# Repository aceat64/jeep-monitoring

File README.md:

# Raspberry Pi Jeep Monitoring System

This system is designed for monitoring or interacting with various functions of my specific Jeep Wrangler, such as the dual battery system and the IHS (Internal High-Speed) CAN bus. All information is available via an API, for consumption by mobile devices or Android headunits on my Jeep's local wifi network.

## Features
- Voltage monitoring of two batteries, for dual battery systems.
- Current monitoring via a shunt resistor, tweaking the code may be required depending on your specific shunt resistor.
- Status of the battery isolator, a 12V digital input.
- Accelerometer, for determining vehicle tilt.
- GPS header, for external GPS module.
- CAN Bus transciever.

## Preview

### Top

### Bottom

## Bill Of Materials
See this [Google doc](https://docs.google.com/spreadsheets/d/1EL97Gz-JKfgCOYKvCzc1mUYXWVdC4jQAL_xUaZWqmfQ/edit?usp=sharing) for more info.

## License
Copyright Andrew LeCody 2017

All schematics, circuit board design files and documentation are released under the [Creative Commons Attribution-ShareAlike 4.0 International License](https://creativecommons.org/licenses/by-sa/4.0/).

All source code is releaed under the [GNU General Public License version 3](https://www.gnu.org/licenses/gpl-3.0-standalone.html).

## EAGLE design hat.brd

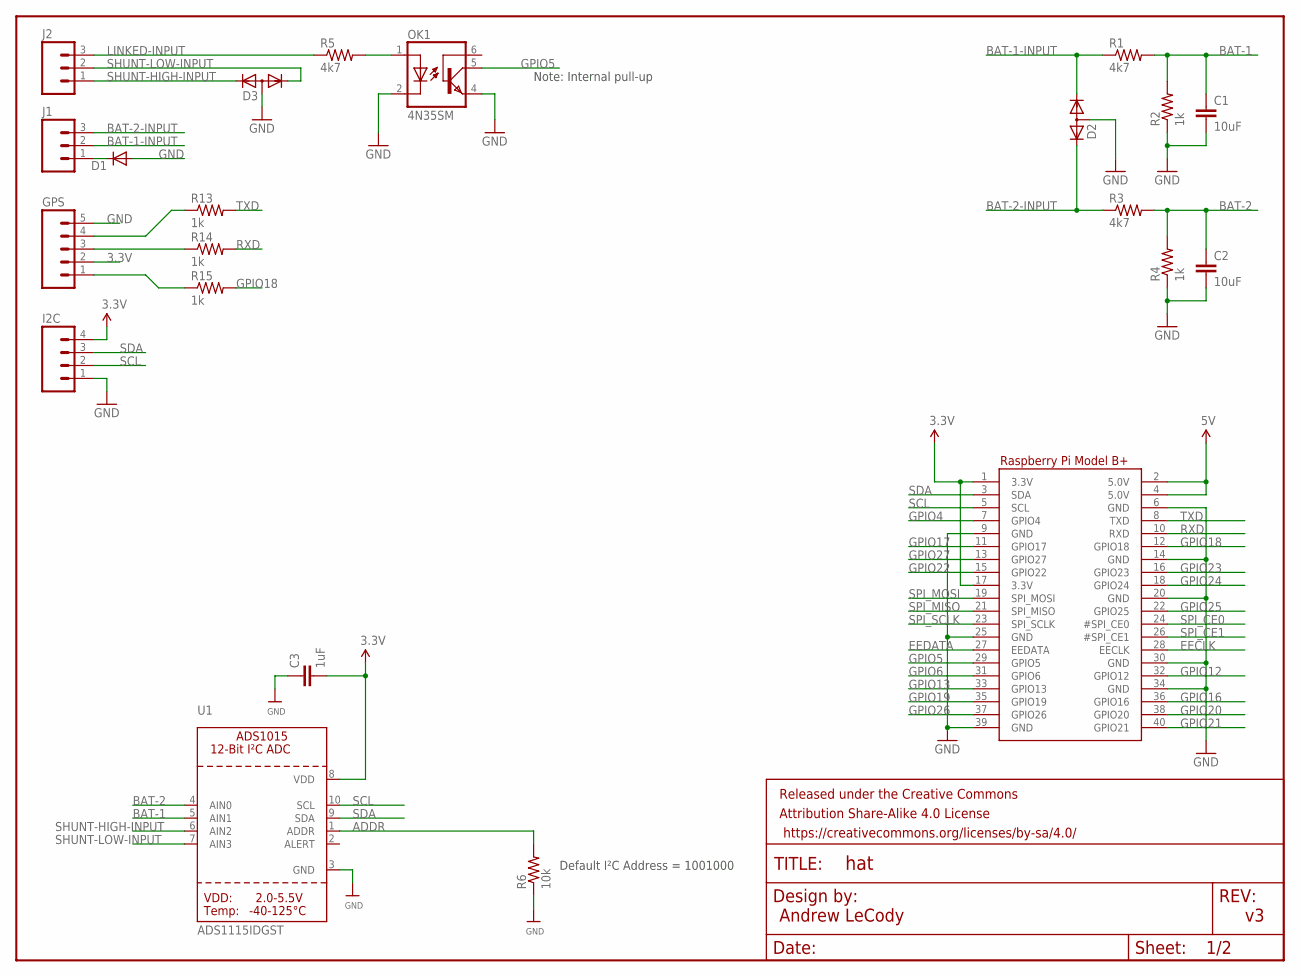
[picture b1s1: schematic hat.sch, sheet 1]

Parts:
C1, C2: 10uF; C0805
C3: 1uF; C0805
D1: DIODE-DO214AC; DO214AC
D2, D3: DIODE-2CA|ACSOT23; SOT23
FRAME1: FRAME-LETTERNO_PACKAGE; DUMMY
GPS: M05PTH; 1X05
I2C: M04PTH; 1X04
J1, J2: M03SCREW; SCREWTERMINAL-3.5MM-3
OK1: 4N35SM; DIL6-SMD
R1, R3, R5: 4k7; R0805
R2, R4, R13, R14, R15: 1k; R0805
R6: 10k; R0805
RPI1: RASPBERRYPI_BPLUS_HATNOSLOTS; PI_HAT_NOSLOTS
U1: ADS1115IDGST; MSOP10

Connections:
3.3V: C3.2, GPS.2, I2C.4, RPI1.1 (3.3V), RPI1.17 (3.3V), U1.8 (VDD); also elsewhere on the board
5V: RPI1.2 (5.0V), RPI1.4 (5.0V); also elsewhere on the board
ADDR: R6.2, U1.1 (ADDR)
BAT-1: C1.1, R1.2, R2.2, U1.5 (AIN1)
BAT-1-INPUT: D2.1 (K1), J1.2, R1.1
BAT-2: C2.1, R3.2, R4.2, U1.4 (AIN0)
BAT-2-INPUT: D2.2 (K2), J1.3, R3.1
EECLK: RPI1.28 (EECLK)
EEDATA: RPI1.27 (EEDATA)
GND: C1.2, C2.2, C3.1, D1.A, D2.3 (A), D3.3 (A), GPS.5, I2C.1, OK1.2 (C), OK1.4 (EMI), R2.1, R4.1, R6.1, RPI1.6 (GND), RPI1.9 (GND), RPI1.14 (GND), RPI1.20 (GND), RPI1.25 (GND), RPI1.30 (GND), RPI1.34 (GND), RPI1.39 (GND), U1.3 (GND); also elsewhere on the board
GPIO4: RPI1.7 (GPIO4)
GPIO5: OK1.5 (COL), RPI1.29 (GPIO5)
GPIO6: RPI1.31 (GPIO6)
GPIO12: RPI1.32 (GPIO12)
GPIO13: RPI1.33 (GPIO13)
GPIO16: RPI1.36 (GPIO16)
GPIO17: RPI1.11 (GPIO17)
GPIO18: R15.2, RPI1.12 (GPIO18)
GPIO19: RPI1.35 (GPIO19)
GPIO20: RPI1.38 (GPIO20)
GPIO21: RPI1.40 (GPIO21)
GPIO22: RPI1.15 (GPIO22)
GPIO23: RPI1.16 (GPIO23)
GPIO24: RPI1.18 (GPIO24)
GPIO25: RPI1.22 (GPIO25); also elsewhere on the board
GPIO26: RPI1.37 (GPIO26)
GPIO27: RPI1.13 (GPIO27)
LINKED-INPUT: J2.3, R5.1
unnamed: GPS.4, R13.1
unnamed: GPS.3, R14.1
unnamed: OK1.1 (A), R5.2
unnamed: GPS.1, R15.1
RXD: R14.2, RPI1.10 (RXD)
SCL: I2C.2, RPI1.5 (SCL), U1.10 (SCL)
SDA: I2C.3, RPI1.3 (SDA), U1.9 (SDA)
SHUNT-HIGH-INPUT: D3.2 (K2), J2.1, U1.6 (AIN2)
SHUNT-LOW-INPUT: D3.1 (K1), J2.2, U1.7 (AIN3)
SPI_CE0: RPI1.24 (#SPI_CE0); also elsewhere on the board
SPI_CE1: RPI1.26 (#SPI_CE1)
SPI_MISO: RPI1.21 (SPI_MISO); also elsewhere on the board
SPI_MOSI: RPI1.19 (SPI_MOSI); also elsewhere on the board
SPI_SCLK: RPI1.23 (SPI_SCLK); also elsewhere on the board
TXD: R13.2, RPI1.8 (TXD)
VEHICLE-GND: D1.C, J1.1

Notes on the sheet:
Andrew LeCody
Default I²C Address = 1001000
Note: Internal pull-up

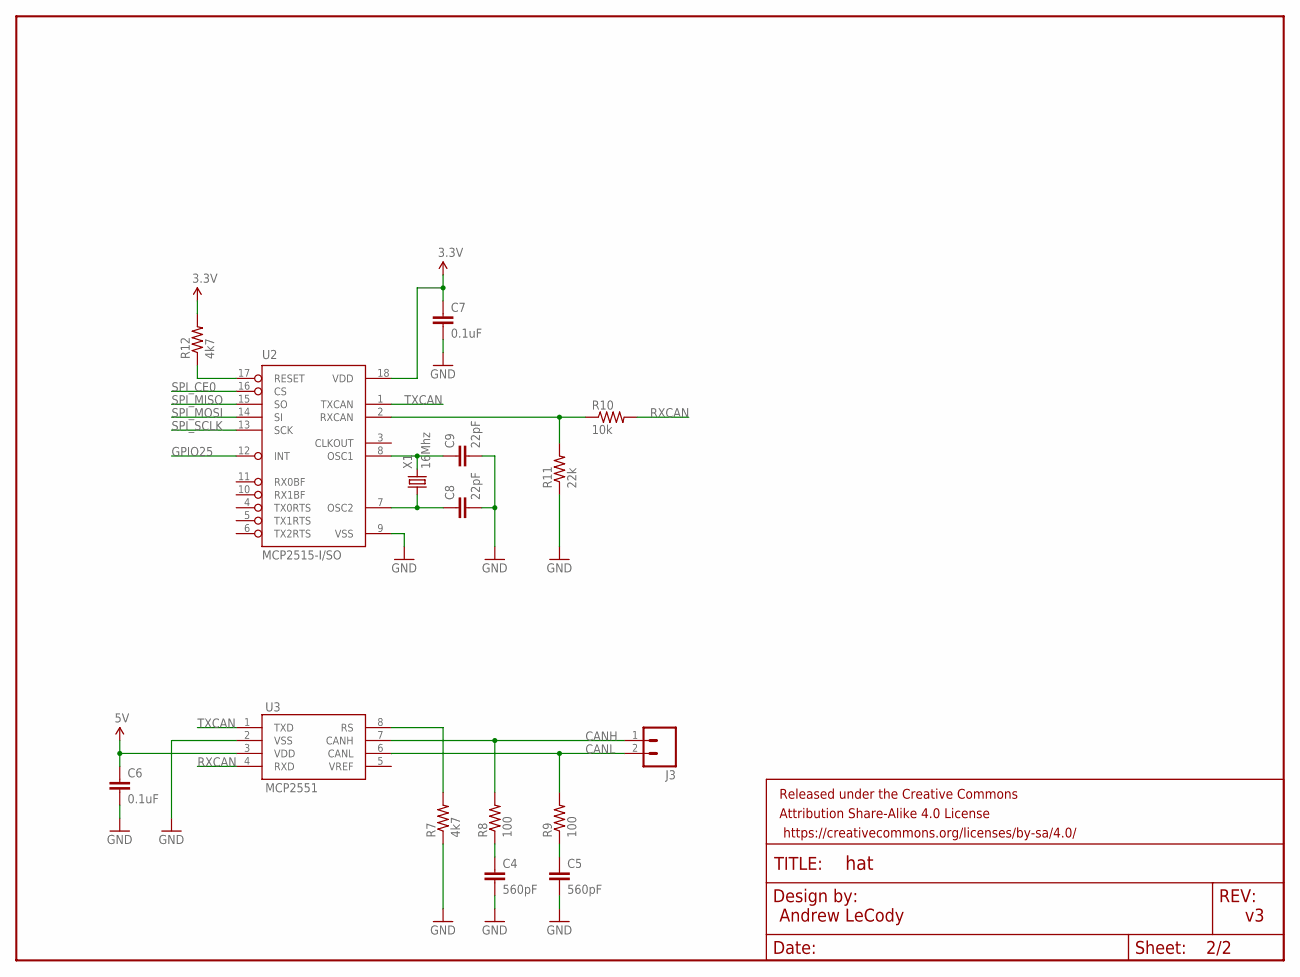
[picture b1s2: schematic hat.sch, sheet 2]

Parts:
C4, C5: 560pF; C0805
C6, C7: 0.1uF; C0805
C8, C9: 22pF; C0805
FRAME2: FRAME-LETTERNO_PACKAGE; DUMMY
J3: M023.5MM; SCREWTERMINAL-3.5MM-2
R7, R12: 4k7; R0805
R8, R9: 100; R0805
R10: 10k; R0805
R11: 22k; R0805
U2: MCP2515-I/SO; SO18L
U3: MCP2551; SO08
X1: 16Mhz; HC49-4-HSMX

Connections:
3.3V: C7.1, R12.2, U2.18 (VDD); also elsewhere on the board
5V: C6.1, U3.3 (VDD); also elsewhere on the board
CANH: J3.1, R8.2, U3.7 (CANH)
CANL: J3.2, R9.2, U3.6 (CANL)
GND: C4.2, C5.2, C6.2, C7.2, C8.2, C9.2, R7.1, R11.1, U2.9 (VSS), U3.2 (VSS); also elsewhere on the board
GPIO25: U2.12 (INT); also elsewhere on the board
unnamed: R10.1, R11.2, U2.2 (RXCAN)
unnamed: C4.1, R8.1
unnamed: C5.1, R9.1
unnamed: C9.1, U2.8 (OSC1), X1.2
unnamed: C8.1, U2.7 (OSC2), X1.1
RS: R7.2, U3.8 (RS)
RXCAN: R10.2, U3.4 (RXD)
SPI_CE0: U2.16 (CS); also elsewhere on the board
SPI_MISO: U2.15 (SO); also elsewhere on the board
SPI_MOSI: U2.14 (SI); also elsewhere on the board
SPI_SCLK: U2.13 (SCK); also elsewhere on the board
TXCAN: U2.1 (TXCAN), U3.1 (TXD)
U2_RST: R12.1, U2.17 (RESET)

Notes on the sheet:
Andrew LeCody

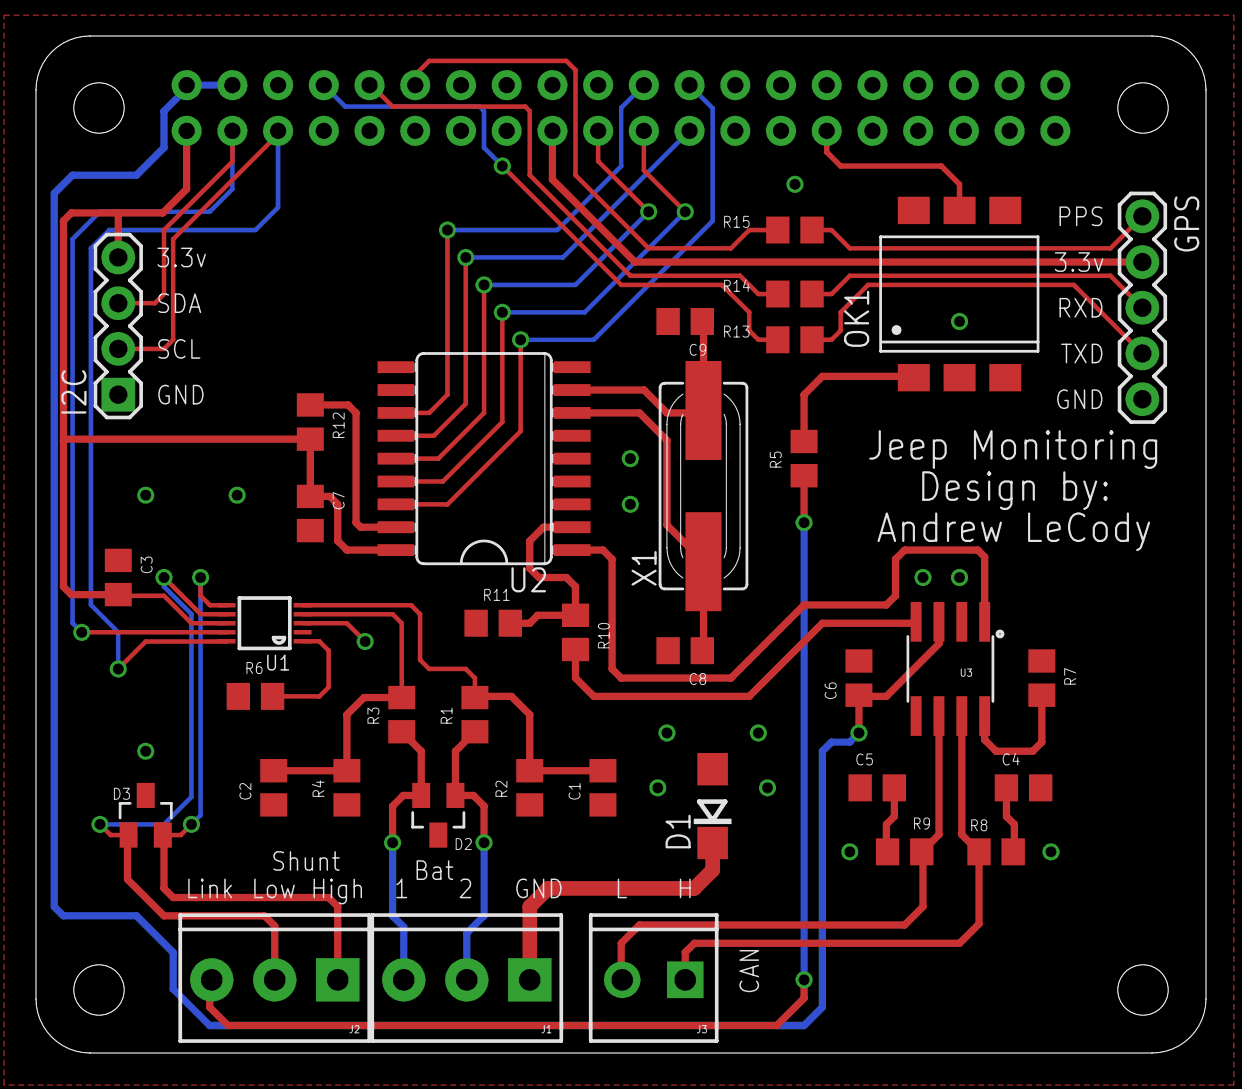
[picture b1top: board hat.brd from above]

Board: 2 copper layers, 65.0 x 56.5 mm, 40 parts (0 on the bottom side), 38 nets.

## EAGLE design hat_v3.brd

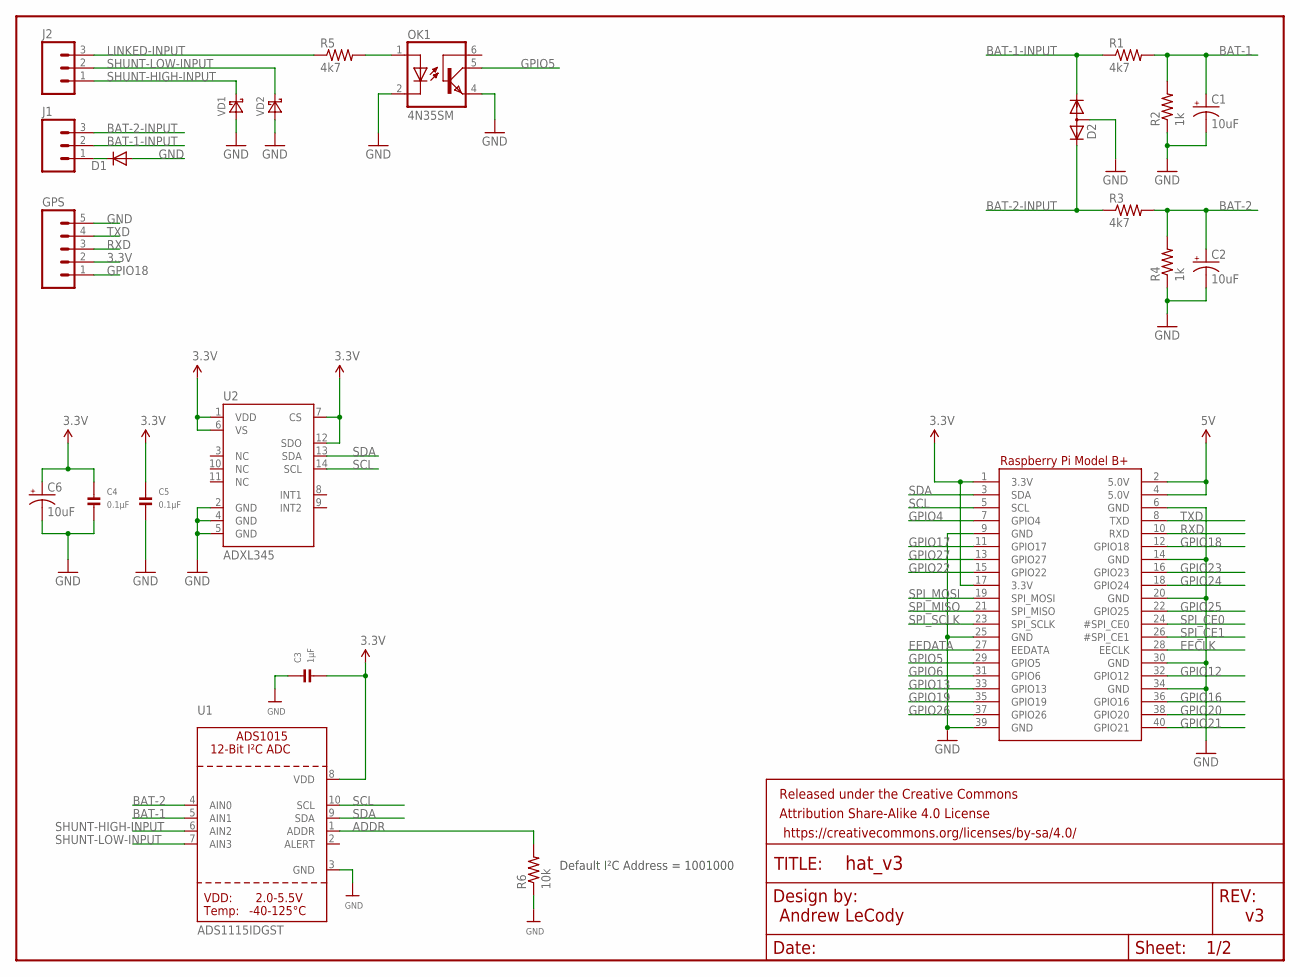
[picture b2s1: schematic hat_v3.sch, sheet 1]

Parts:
C1, C2, C6: 10uF; EIA3216
C3: 1µF; 0805
C4, C5: 0.1µF; 0805
D1: DIODE-DO214AC; DO214AC
D2: DIODE-2CA|ACSOT23; SOT23
FRAME1: FRAME-LETTER; CREATIVE_COMMONS
GPS: M05PTH; 1X05
J1, J2: M03-SCREW-5MM; SCREWTERMINAL-5MM-3
OK1: 4N35SM; DIL6-SMD
R1, R3, R5: 4k7; 0805
R2, R4: 1k; 0805
R6: 10k; 0805
RPI1: RASPBERRYPI_BPLUS_HATNOSLOTS; PI_HAT_NOSLOTS
U1: ADS1115IDGST; MSOP10
U2: ADXL345; LGA14
VD1, VD2: DIODE-SCHOTTKY-SOD523; SOD523

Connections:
3.3V: C3.2, C4.1, C5.1, C6.A (+), GPS.2, RPI1.1 (3.3V), RPI1.17 (3.3V), U1.8 (VDD), U2.1 (VDD), U2.6 (VS), U2.7 (CS), U2.12 (SDO); also elsewhere on the board
5V: RPI1.2 (5.0V), RPI1.4 (5.0V); also elsewhere on the board
ADDR: R6.2, U1.1 (ADDR)
BAT-1: C1.A (+), R1.2, R2.2, U1.5 (AIN1)
BAT-1-INPUT: D2.1 (K1), J1.2, R1.1
BAT-2: C2.A (+), R3.2, R4.2, U1.4 (AIN0)
BAT-2-INPUT: D2.2 (K2), J1.3, R3.1
EECLK: RPI1.28 (EECLK)
EEDATA: RPI1.27 (EEDATA)
GND: C1.C (-), C2.C (-), C3.1, C4.2, C5.2, C6.C (-), D1.A, D2.3 (A), GPS.5, OK1.2 (C), OK1.4 (EMI), R2.1, R4.1, R6.1, RPI1.6 (GND), RPI1.9 (GND), RPI1.14 (GND), RPI1.20 (GND), RPI1.25 (GND), RPI1.30 (GND), RPI1.34 (GND), RPI1.39 (GND), U1.3 (GND), U2.2 (GND), U2.4 (GND), U2.5 (GND), VD1.A, VD2.A; also elsewhere on the board
GPIO4: RPI1.7 (GPIO4)
GPIO5: OK1.5 (COL), RPI1.29 (GPIO5)
GPIO6: RPI1.31 (GPIO6)
GPIO12: RPI1.32 (GPIO12)
GPIO13: RPI1.33 (GPIO13)
GPIO16: RPI1.36 (GPIO16)
GPIO17: RPI1.11 (GPIO17)
GPIO18: GPS.1, RPI1.12 (GPIO18)
GPIO19: RPI1.35 (GPIO19)
GPIO20: RPI1.38 (GPIO20)
GPIO21: RPI1.40 (GPIO21)
GPIO22: RPI1.15 (GPIO22)
GPIO23: RPI1.16 (GPIO23)
GPIO24: RPI1.18 (GPIO24)
GPIO25: RPI1.22 (GPIO25); also elsewhere on the board
GPIO26: RPI1.37 (GPIO26)
GPIO27: RPI1.13 (GPIO27)
LINKED-INPUT: J2.3, R5.1
unnamed: OK1.1 (A), R5.2
RXD: GPS.3, RPI1.10 (RXD)
SCL: RPI1.5 (SCL), U1.10 (SCL), U2.14 (SCL)
SDA: RPI1.3 (SDA), U1.9 (SDA), U2.13 (SDA)
SHUNT-HIGH-INPUT: J2.1, U1.6 (AIN2), VD1.C
SHUNT-LOW-INPUT: J2.2, U1.7 (AIN3), VD2.C
SPI_CE0: RPI1.24 (#SPI_CE0); also elsewhere on the board
SPI_CE1: RPI1.26 (#SPI_CE1)
SPI_MISO: RPI1.21 (SPI_MISO); also elsewhere on the board
SPI_MOSI: RPI1.19 (SPI_MOSI); also elsewhere on the board
SPI_SCLK: RPI1.23 (SPI_SCLK); also elsewhere on the board
TXD: GPS.4, RPI1.8 (TXD)
VEHICLE-GND: D1.C, J1.1

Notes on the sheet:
Andrew LeCody
Default I²C Address = 1001000

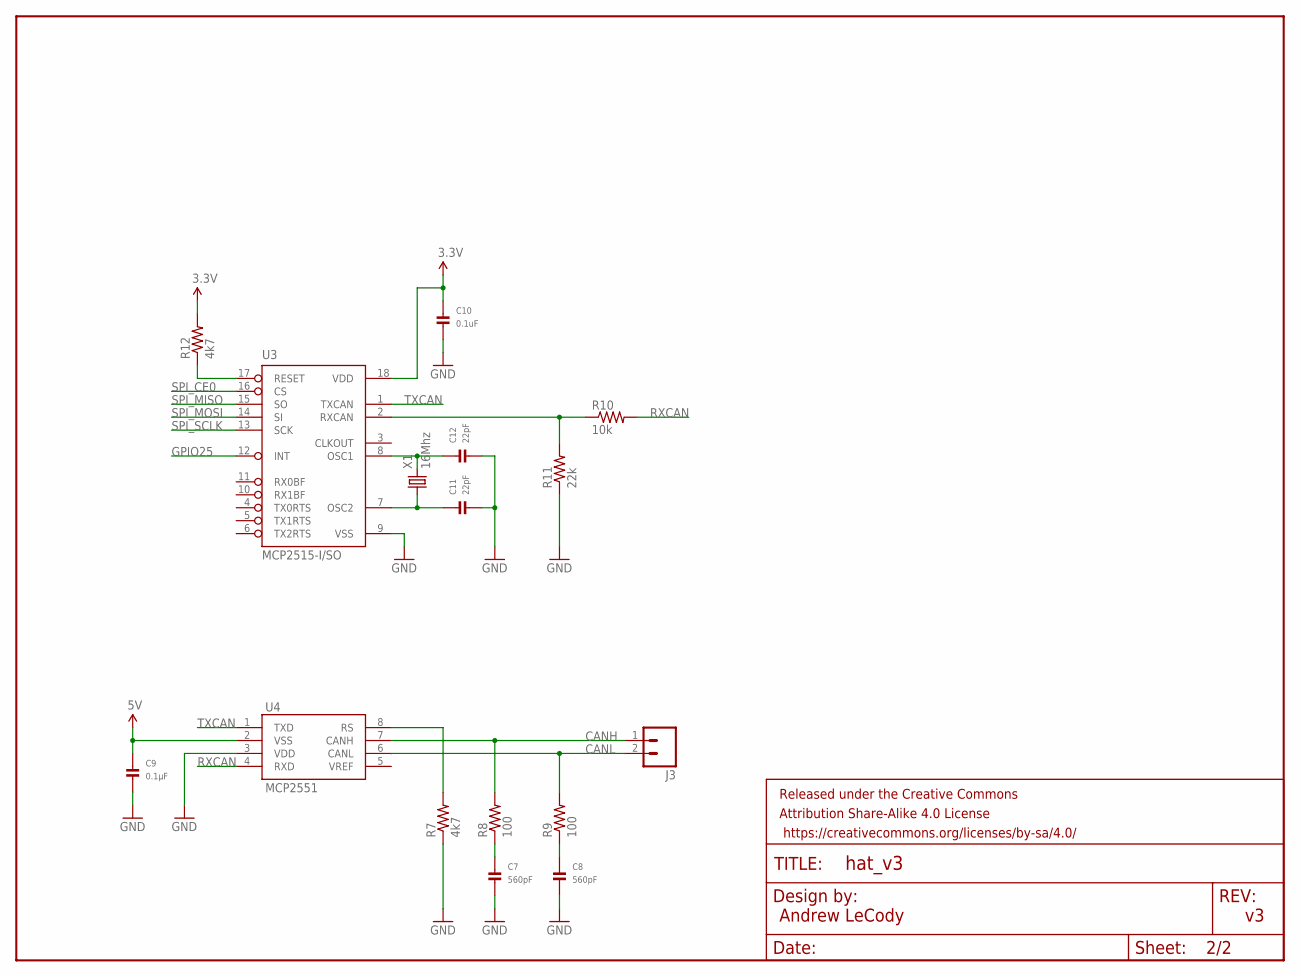
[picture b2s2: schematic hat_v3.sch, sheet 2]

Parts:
C7, C8: 560pF; 0805
C9: 0.1µF; 0805
C10: 0.1uF; 0805
C11, C12: 22pF; 0805
FRAME2: FRAME-LETTERNO_PACKAGE; DUMMY
J3: M025MM; SCREWTERMINAL-5MM-2
R7, R12: 4k7; 0805
R8, R9: 100; 0805
R10: 10k; 0805
R11: 22k; 0805
U3: MCP2515-I/SO; SO18L
U4: MCP2551; SO08
X1: 16Mhz; HC49-4-HSMX

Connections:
3.3V: C10.1, R12.2, U3.18 (VDD); also elsewhere on the board
5V: C9.1, U4.2 (VSS); also elsewhere on the board
CANH: J3.1, R8.2, U4.7 (CANH)
CANL: J3.2, R9.2, U4.6 (CANL)
GND: C7.2, C8.2, C9.2, C10.2, C11.2, C12.2, R7.1, R11.1, U3.9 (VSS), U4.3 (VDD); also elsewhere on the board
GPIO25: U3.12 (INT); also elsewhere on the board
unnamed: R10.1, R11.2, U3.2 (RXCAN)
unnamed: C7.1, R8.1
unnamed: C8.1, R9.1
unnamed: C12.1, U3.8 (OSC1), X1.2
unnamed: C11.1, U3.7 (OSC2), X1.1
RS: R7.2, U4.8 (RS)
RXCAN: R10.2, U4.4 (RXD)
SPI_CE0: U3.16 (CS); also elsewhere on the board
SPI_MISO: U3.15 (SO); also elsewhere on the board
SPI_MOSI: U3.14 (SI); also elsewhere on the board
SPI_SCLK: U3.13 (SCK); also elsewhere on the board
TXCAN: U3.1 (TXCAN), U4.1 (TXD)
U5_RST: R12.1, U3.17 (RESET)

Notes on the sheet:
Andrew LeCody

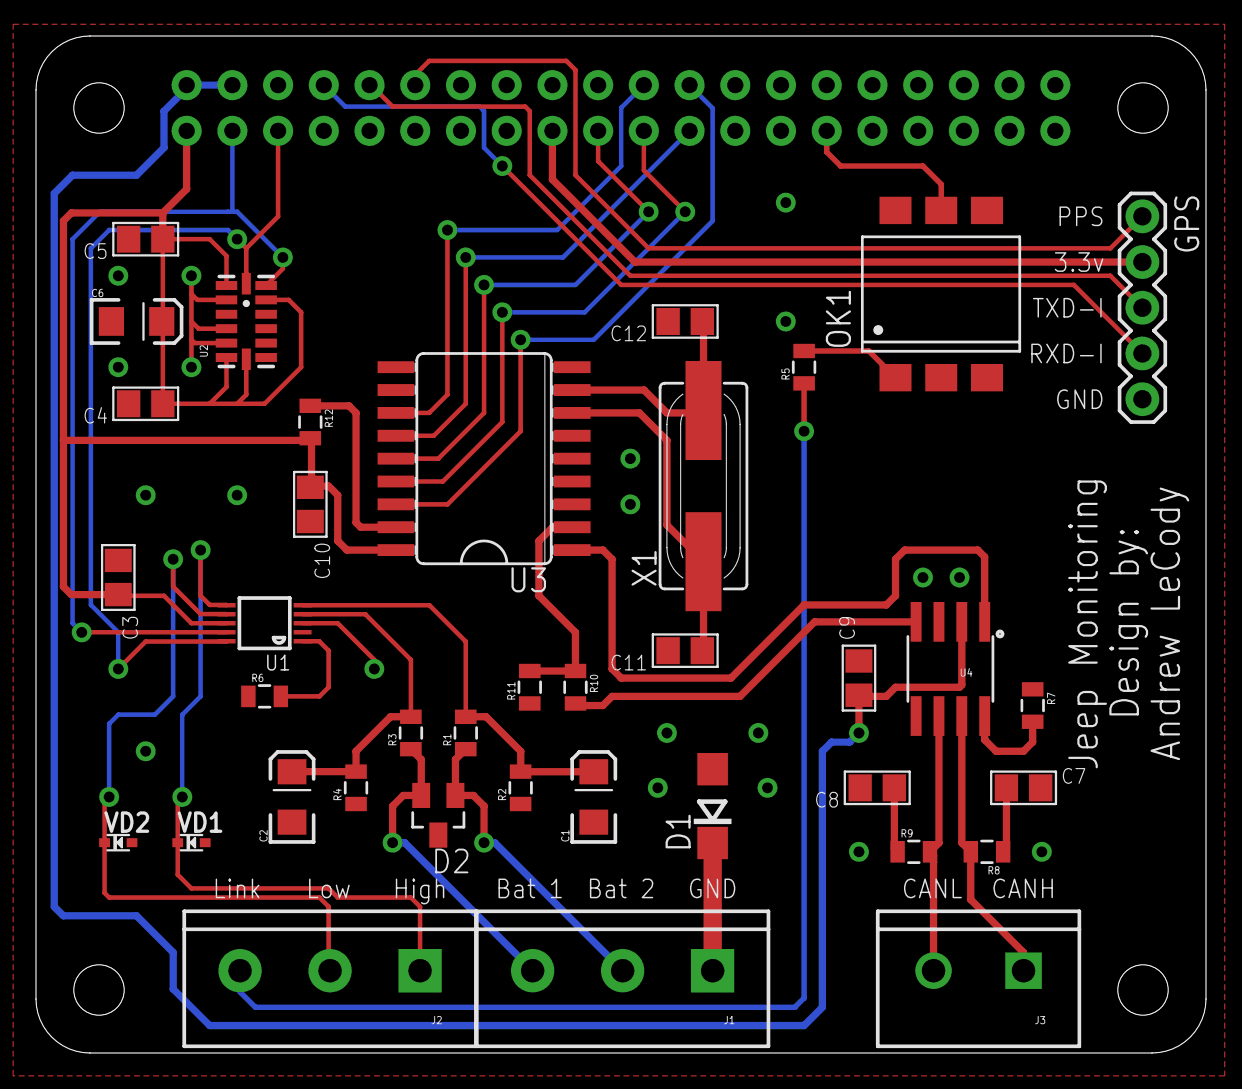
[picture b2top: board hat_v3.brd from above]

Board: 2 copper layers, 65.0 x 56.5 mm, 41 parts (0 on the bottom side), 35 nets.

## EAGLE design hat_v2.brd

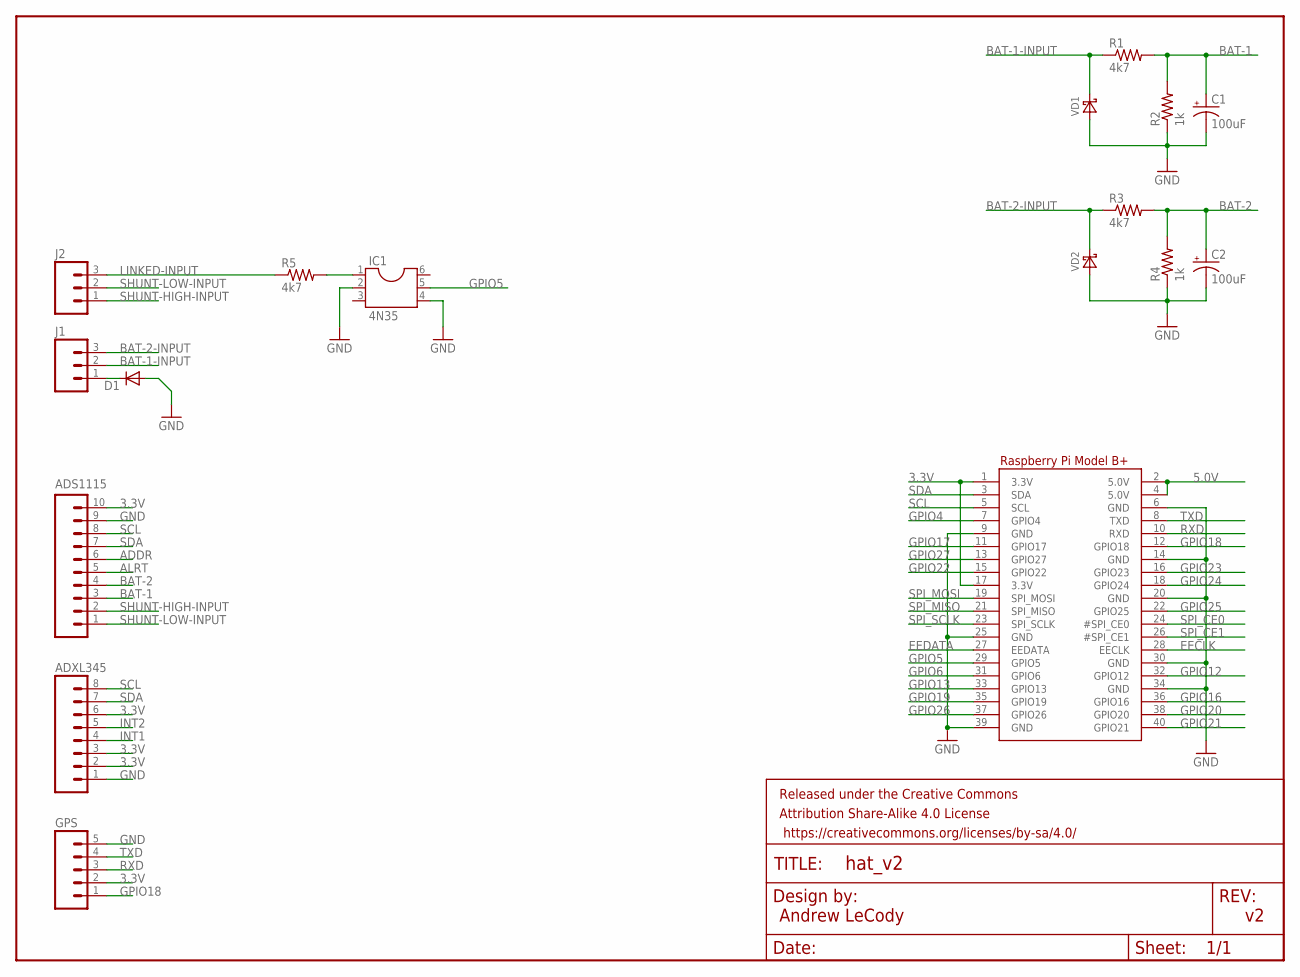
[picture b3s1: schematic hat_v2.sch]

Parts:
ADS1115: M10SILK_FEMALE_PTH; 1X10
ADXL345: M08SILK_FEMALE_PTH; 1X08
C1, C2: 100uF; CPOL-RADIAL-100UF-25V
D1: DIODE-DO41-10; DO41-10
FRAME1: FRAME-LETTER; CREATIVE_COMMONS
GPS: M05PTH; 1X05
IC1: 4N35; DIL06
J1, J2: M03-SCREW-5MM; SCREWTERMINAL-5MM-3
R1, R3, R5: 4k7; AXIAL-0.3
R2, R4: 1k; AXIAL-0.3
RPI1: RASPBERRYPI_BPLUS_HATNOSLOTS; PI_HAT_NOSLOTS
VD1, VD2: DIODE-SCHOTTKY-DO201AD; DO201AD

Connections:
3.3V: ADS1115.10, ADXL345.2, ADXL345.3, ADXL345.6, GPS.2, RPI1.1 (3.3V), RPI1.17 (3.3V)
5.0V: RPI1.2 (5.0V), RPI1.4 (5.0V)
ADDR: ADS1115.6
ALRT: ADS1115.5
BAT-1: ADS1115.3, C1.1 (+), R1.P$2 (2), R2.P$2 (2)
BAT-1-INPUT: J1.2, R1.P$1 (1), VD1.C
BAT-2: ADS1115.4, C2.1 (+), R3.P$2 (2), R4.P$2 (2)
BAT-2-INPUT: J1.3, R3.P$1 (1), VD2.C
EECLK: RPI1.28 (EECLK)
EEDATA: RPI1.27 (EEDATA)
GND: ADS1115.9, ADXL345.1, C1.2 (-), C2.2 (-), D1.A, GPS.5, IC1.2, IC1.4, R2.P$1 (1), R4.P$1 (1), RPI1.6 (GND), RPI1.9 (GND), RPI1.14 (GND), RPI1.20 (GND), RPI1.25 (GND), RPI1.30 (GND), RPI1.34 (GND), RPI1.39 (GND), VD1.A, VD2.A
GPIO4: RPI1.7 (GPIO4)
GPIO5: IC1.5, RPI1.29 (GPIO5)
GPIO6: RPI1.31 (GPIO6)
GPIO12: RPI1.32 (GPIO12)
GPIO13: RPI1.33 (GPIO13)
GPIO16: RPI1.36 (GPIO16)
GPIO17: RPI1.11 (GPIO17)
GPIO18: GPS.1, RPI1.12 (GPIO18)
GPIO19: RPI1.35 (GPIO19)
GPIO20: RPI1.38 (GPIO20)
GPIO21: RPI1.40 (GPIO21)
GPIO22: RPI1.15 (GPIO22)
GPIO23: RPI1.16 (GPIO23)
GPIO24: RPI1.18 (GPIO24)
GPIO25: RPI1.22 (GPIO25)
GPIO26: RPI1.37 (GPIO26)
GPIO27: RPI1.13 (GPIO27)
INT1: ADXL345.4
INT2: ADXL345.5
LINKED-INPUT: J2.3, R5.P$1 (1)
unnamed: D1.C, J1.1
unnamed: IC1.1, R5.P$2 (2)
RXD: GPS.3, RPI1.10 (RXD)
SCL: ADS1115.8, ADXL345.8, RPI1.5 (SCL)
SDA: ADS1115.7, ADXL345.7, RPI1.3 (SDA)
SHUNT-HIGH-INPUT: ADS1115.2, J2.1
SHUNT-LOW-INPUT: ADS1115.1, J2.2
SPI_CE0: RPI1.24 (#SPI_CE0)
SPI_CE1: RPI1.26 (#SPI_CE1)
SPI_MISO: RPI1.21 (SPI_MISO)
SPI_MOSI: RPI1.19 (SPI_MOSI)
SPI_SCLK: RPI1.23 (SPI_SCLK)
TXD: GPS.4, RPI1.8 (TXD)

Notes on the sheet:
Andrew LeCody

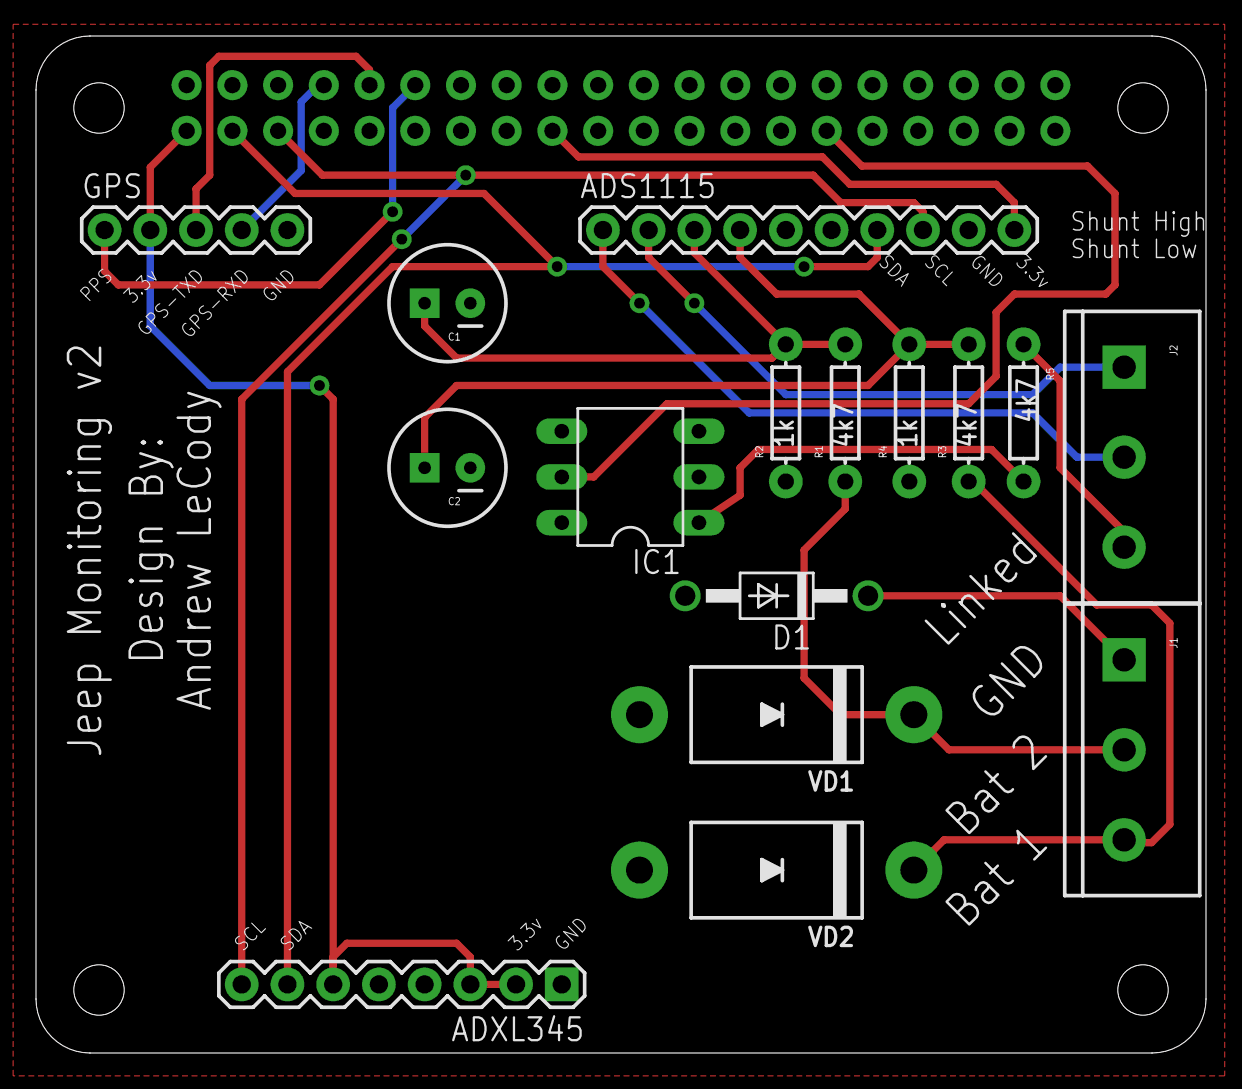
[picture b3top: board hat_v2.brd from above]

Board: 2 copper layers, 65.0 x 56.5 mm, 18 parts (0 on the bottom side), 18 nets.

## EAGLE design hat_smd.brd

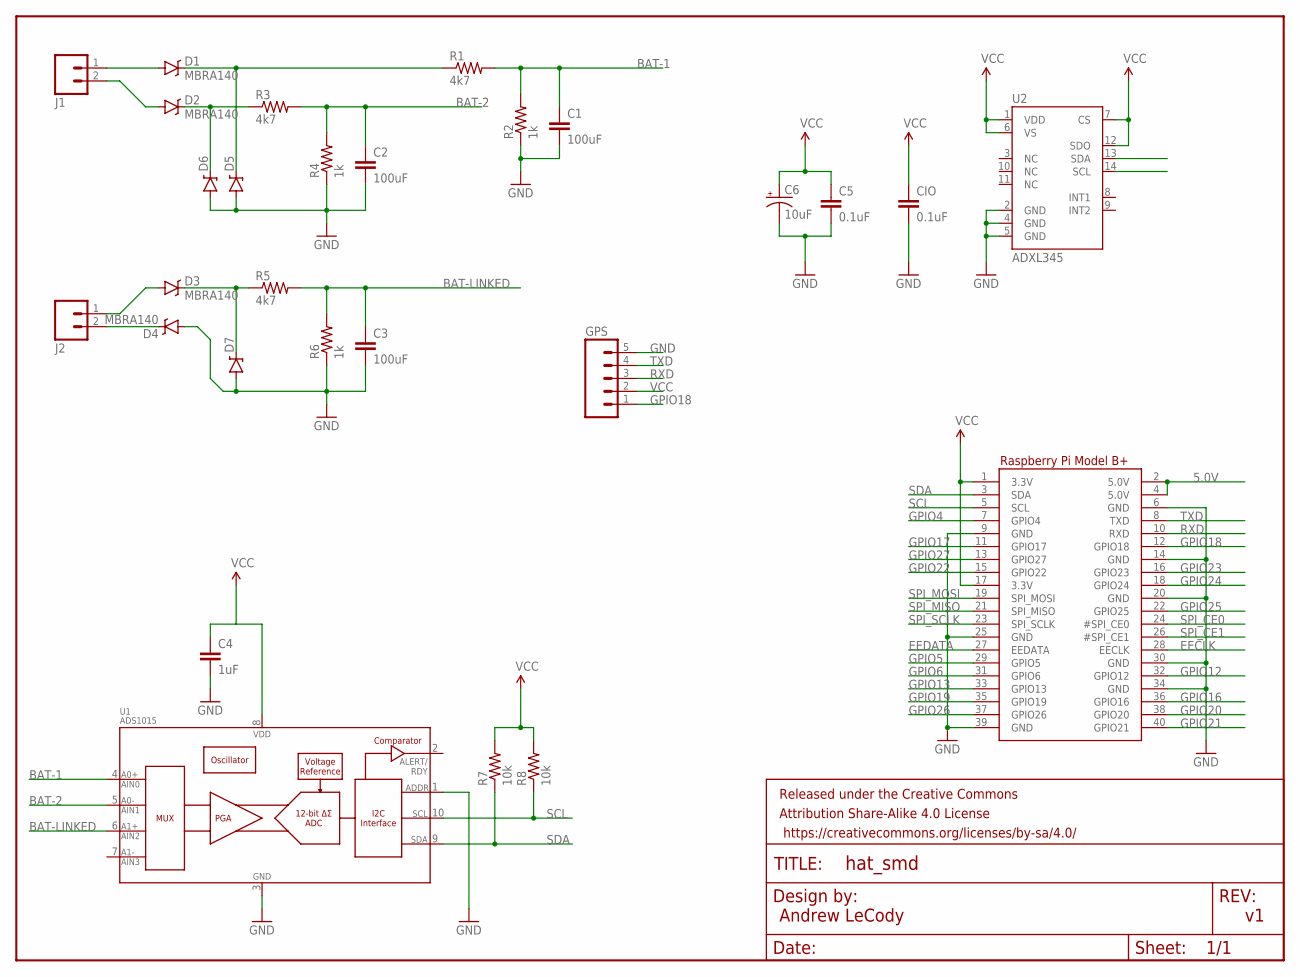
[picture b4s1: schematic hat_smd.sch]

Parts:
C1, C2, C3: 100uF; 0603-CAP
C4: 1uF; 0603-CAP
C5: 0.1uF; 0603-CAP
C6: 10uF; EIA3216
CIO: 0.1uF; 0603-CAP
D1, D2, D3, D4: MBRA140; SMA-DIODE
D5, D6, D7: DIODE-ZENERSMB; SMB-DIODE
FRAME1: FRAME-LETTER; CREATIVE_COMMONS
GPS: M05PTH; 1X05
J1, J2: M025MM; SCREWTERMINAL-5MM-2
R1, R3, R5: 4k7; 0603-RES
R2, R4, R6: 1k; 0603-RES
R7, R8: 10k; 0603-RES
RPI1: RASPBERRYPI_BPLUS_HATNOSLOTS; PI_HAT_NOSLOTS
U1: ADS1015; MSOP10
U2: ADXL345; LGA14

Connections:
5.0V: RPI1.2 (5.0V), RPI1.4 (5.0V)
BAT-1: C1.1, R1.2, R2.2, U1.4 (AIN0)
BAT-2: C2.1, R3.2, R4.2, U1.5 (AIN1)
BAT-LINKED: C3.1, R5.2, R6.2, U1.6 (AIN2)
EECLK: RPI1.28 (EECLK)
EEDATA: RPI1.27 (EEDATA)
GND: C1.2, C2.2, C3.2, C4.2, C5.2, C6.C (-), CIO.2, D4.A, D5.A, D6.A, D7.A, GPS.5, R2.1, R4.1, R6.1, RPI1.6 (GND), RPI1.9 (GND), RPI1.14 (GND), RPI1.20 (GND), RPI1.25 (GND), RPI1.30 (GND), RPI1.34 (GND), RPI1.39 (GND), U1.1 (ADDR), U1.3 (VSS), U2.2 (GND), U2.4 (GND), U2.5 (GND)
GPIO4: RPI1.7 (GPIO4)
GPIO5: RPI1.29 (GPIO5)
GPIO6: RPI1.31 (GPIO6)
GPIO12: RPI1.32 (GPIO12)
GPIO13: RPI1.33 (GPIO13)
GPIO16: RPI1.36 (GPIO16)
GPIO17: RPI1.11 (GPIO17)
GPIO18: GPS.1, RPI1.12 (GPIO18)
GPIO19: RPI1.35 (GPIO19)
GPIO20: RPI1.38 (GPIO20)
GPIO21: RPI1.40 (GPIO21)
GPIO22: RPI1.15 (GPIO22)
GPIO23: RPI1.16 (GPIO23)
GPIO24: RPI1.18 (GPIO24)
GPIO25: RPI1.22 (GPIO25)
GPIO26: RPI1.37 (GPIO26)
GPIO27: RPI1.13 (GPIO27)
unnamed: D1.A, J1.1
unnamed: D2.A, J1.2
unnamed: D3.A, J2.1
unnamed: D4.C, J2.2
unnamed: D1.C, D5.C, R1.1
unnamed: D2.C, D6.C, R3.1
unnamed: D3.C, D7.C, R5.1
RXD: GPS.3, RPI1.10 (RXD)
SCL: R8.1, RPI1.5 (SCL), U1.10 (SCL), U2.14 (SCL)
SDA: R7.1, RPI1.3 (SDA), U1.9 (SDA), U2.13 (SDA)
SPI_CE0: RPI1.24 (#SPI_CE0)
SPI_CE1: RPI1.26 (#SPI_CE1)
SPI_MISO: RPI1.21 (SPI_MISO)
SPI_MOSI: RPI1.19 (SPI_MOSI)
SPI_SCLK: RPI1.23 (SPI_SCLK)
TXD: GPS.4, RPI1.8 (TXD)
VCC: C4.1, C5.1, C6.A (+), CIO.1, GPS.2, R7.2, R8.2, RPI1.1 (3.3V), RPI1.17 (3.3V), U1.8 (VDD), U2.1 (VDD), U2.6 (VS), U2.7 (CS), U2.12 (SDO)

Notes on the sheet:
Andrew LeCody

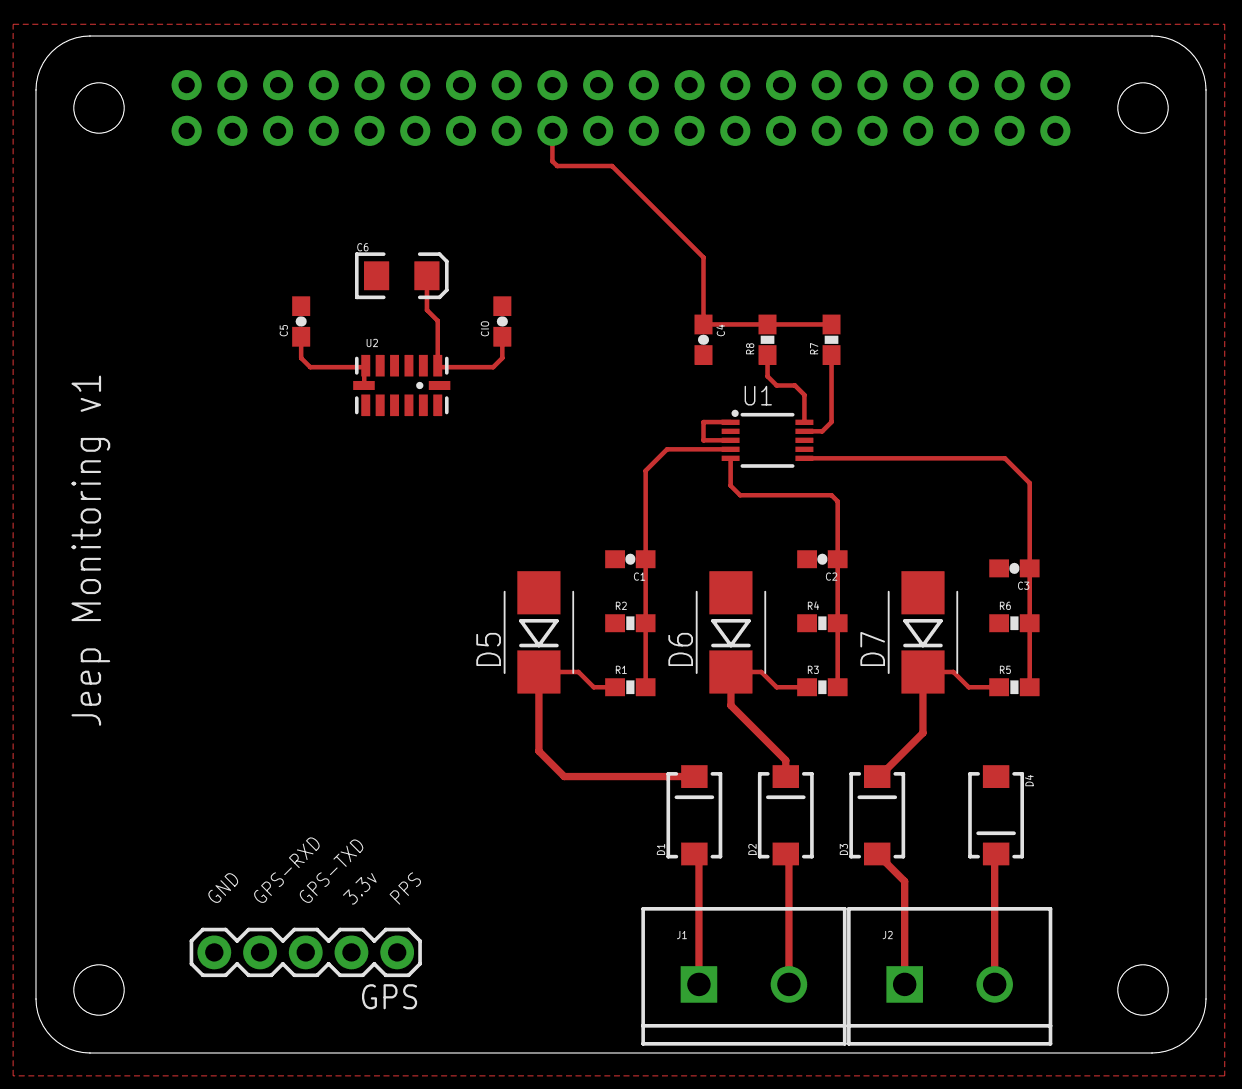
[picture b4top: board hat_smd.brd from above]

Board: 2 copper layers, 65.0 x 56.5 mm, 29 parts (0 on the bottom side), 18 nets.

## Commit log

2016-10-28 Renamed hat2 to hat_smd
2016-12-06 Current monitoring
2016-12-09 V2 board done
2016-12-18 Minor tweak to PCB
2016-12-18 Version 3 mostly done
2016-12-19 Minor tweaks to v2
2016-12-19 V3 almost done, just need to finish MCP2515
2016-12-19 V3 done!
2016-12-19 Switch to round vias for all non-GND vias
2016-12-19 Switch to round vias for all non-GND vias (v2)
2016-12-20 Reworked v3
2016-12-21 Tweaked placement of a via for ground
2016-12-22 Minor tweaks to GND plane
2016-12-24 Switched to 3.5mm screw terminals
2017-01-02 Version 3 ready for public
2017-01-02 Cleanup text
2017-01-02 Added PNG files for board
2017-01-02 Added images to README.md
2017-01-02 Link to correct images
2017-01-02 Minor tweak to README.md
2017-01-02 Added license info for API
2017-01-02 Added link to BOM
2017-01-03 Added 1kOhm resistors on inputs
2017-01-03 Changed to packages with larger pads for easier hand soldering
2017-01-03 Tweaked spacing for two resistors
2017-01-04 Replaced TVS diodes VD1/VD2 with single TVS diode D3
2017-01-04 Properly connect U5 to 3V3
2017-01-05 Added X/Y/Z markings for adxl345
2017-01-14 Replaced accelerometer with i2c header
2017-01-17 Rename U5_RST to U2_RST
2017-01-17 Minor tweak to silkscreen
2017-02-18 Minor tweak to ground plane
2017-04-29 Fixed power for MCP2551

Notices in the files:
parts and their libraries:
microbuilder: This work is placed in the public domain, and may be freely used for commercial and non-commercial work with the following conditions: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
SparkFun-Aesthetics: Licensing: Creative Commons ShareAlike 4.0 International - https://creativecommons.org/licenses/by-sa/4.0
